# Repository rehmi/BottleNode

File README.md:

# BottleNode
#### An interactive network node for immersive experiences built around a Seeed Studio XIAO ESP32-S3

This repository contains the design and code for the BottleNode project. The project is structured into two main directories:

- `AllInOne_test`: This directory contains an Arduino program to test the BottleNode hardware. You will want to install the following Arduino libraries using the Library Manager (`Sketch` -> `Include Library` -> `Manage Libraries...`):
	* `Adafruit NeoPixel` (by Adafruit)
	* `LiteLED` (by Xylopyrographer)
	* `OSC` (by Adrian Freed)
	* `WS2812FX` (by Harm Aldick)

- The program also depends on the [ESP32-audioI2S library](https://github.com/schreibfaul1/ESP32-audioI2S), which you can install in the Arduino IDE by following these steps:

 	1. Download the latest release as a .zip from the repo `Releases` page [(link)](https://github.com/schreibfaul1/ESP32-audioI2S/archive/refs/tags/3.0.0.zip)
	2. Click on `Sketch` -> `Include Library` -> `Add .ZIP Library...` to add the library to your environment.
	
- `hw/BottleNode`: This directory contains the KiCAD project and associated files for the hardware design of the BottleNode. It includes 3D renderings of the board as PNG images and a PDF schematic of the board. You can view the schematic [here](hw/BottleNode/BottleNode%20schematic.pdf).

	Renderings of the top and bottom of the PCB:

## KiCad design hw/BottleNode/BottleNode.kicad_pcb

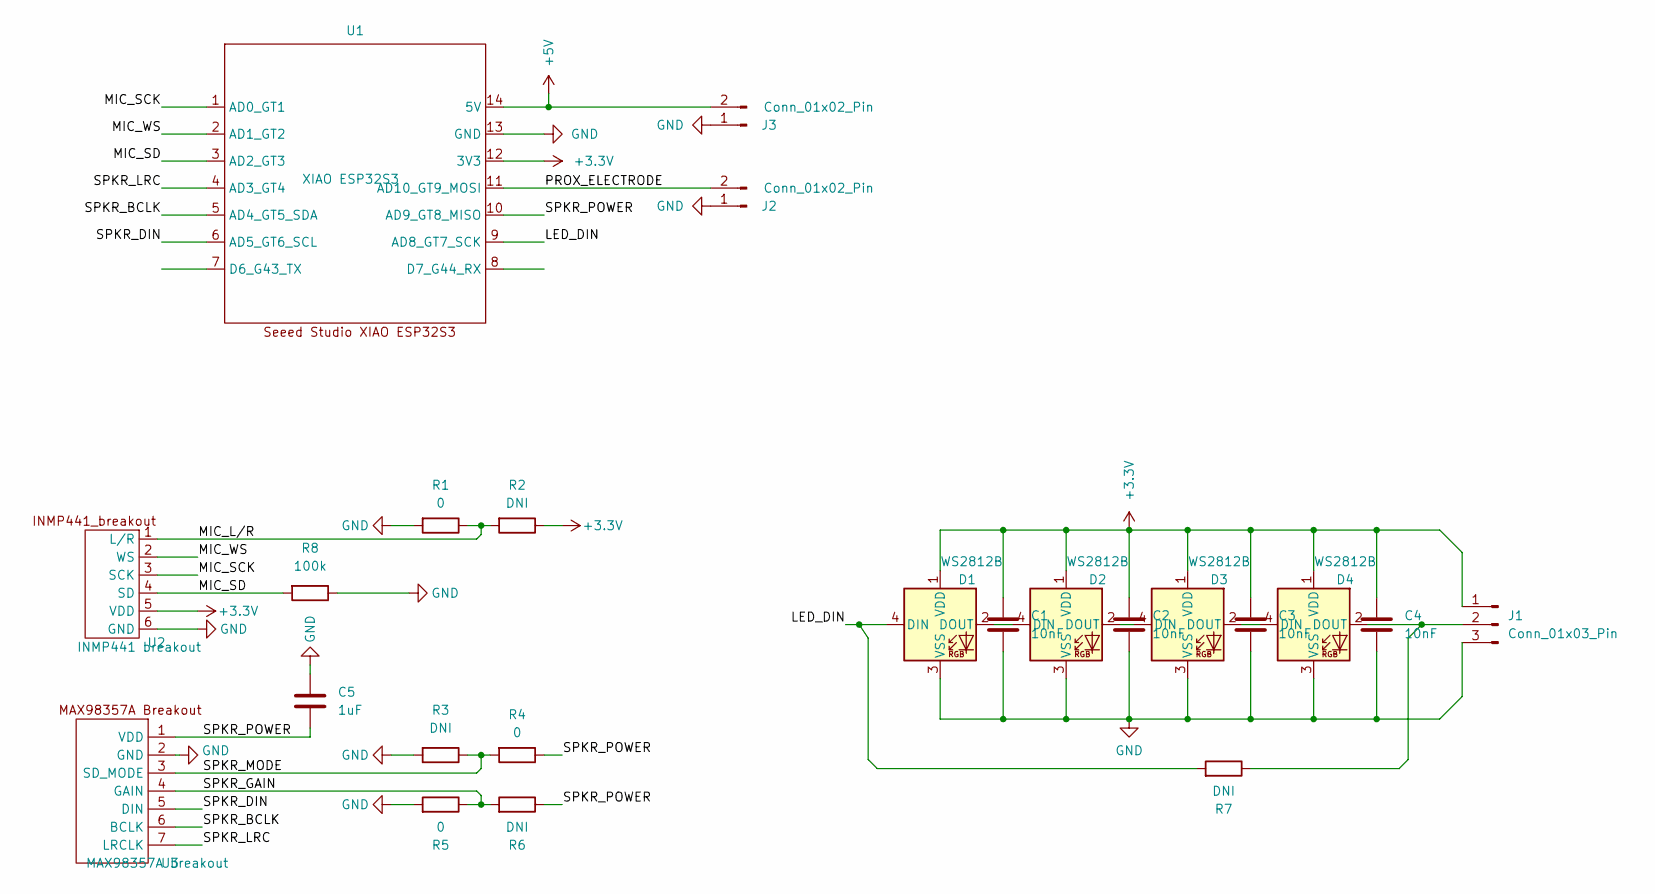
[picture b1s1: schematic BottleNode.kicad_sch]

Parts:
C1, C2, C3, C4: 10nF; C_0603_1608Metric_Pad1.08x0.95mm_HandSolder
C5: 1uF; C_0603_1608Metric_Pad1.08x0.95mm_HandSolder
D1, D2, D3, D4: WS2812B; LED_WS2812B_PLCC4_5.0x5.0mm_P3.2mm
J1: Conn_01x03_Pin; PinHeader_1x03_P2.54mm_Vertical
J2, J3: Conn_01x02_Pin; PinHeader_1x02_P2.54mm_Vertical
R1, R4, R5: 0; R_0603_1608Metric_Pad0.98x0.95mm_HandSolder
R2, R3, R6, R7: DNI; R_0603_1608Metric_Pad0.98x0.95mm_HandSolder
R8: 100k; R_0603_1608Metric_Pad0.98x0.95mm_HandSolder
U1: XIAO ESP32S3; XIAO-Generic-Thruhole-14P-2.54-21X17.8MM
U2: INMP441 breakout; INMP441_breakout
U3: MAX98357A breakout; MAX98357A_adafruit_breakout

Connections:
+3.3V: C1.1, C2.1, C3.1, C4.1, D1.1 (VDD), D2.1 (VDD), D3.1 (VDD), D4.1 (VDD), J1.1, R2.1, U1.12 (3V3), U2.5 (VDD)
+5V: J3.2, U1.14 (5V)
/LED_DIN: D1.4 (DIN), R7.2, U1.9 (AD8_GT7_SCK)
/MIC_L/R: R1.1, R2.2, U2.1 (L/R)
/MIC_SCK: U1.1 (AD0_GT1), U2.3 (SCK)
/MIC_SD: R8.2, U1.3 (AD2_GT3), U2.4 (SD)
/MIC_WS: U1.2 (AD1_GT2), U2.2 (WS)
/PROX_ELECTRODE: J2.2, U1.11 (AD10_GT9_MOSI)
/SPKR_BCLK: U1.5 (AD4_GT5_SDA), U3.6 (BCLK)
/SPKR_DIN: U1.6 (AD5_GT6_SCL), U3.5 (DIN)
/SPKR_GAIN: R5.1, R6.2, U3.4 (GAIN)
/SPKR_LRC: U1.4 (AD3_GT4), U3.7 (LRCLK)
/SPKR_MODE: R3.1, R4.2, U3.3 (SD_MODE)
/SPKR_POWER: C5.2, R4.1, R6.1, U1.10 (AD9_GT8_MISO), U3.1 (VDD)
GND: C1.2, C2.2, C3.2, C4.2, C5.1, D1.3 (VSS), D2.3 (VSS), D3.3 (VSS), D4.3 (VSS), J1.3, J2.1, J3.1, R1.2, R3.2, R5.2, R8.1, U1.13 (GND), U2.6 (GND), U3.2 (GND)
unnamed: D1.2 (DOUT), D2.4 (DIN)
unnamed: D2.2 (DOUT), D3.4 (DIN)
unnamed: D3.2 (DOUT), D4.4 (DIN)
unnamed: D4.2 (DOUT), J1.2, R7.1

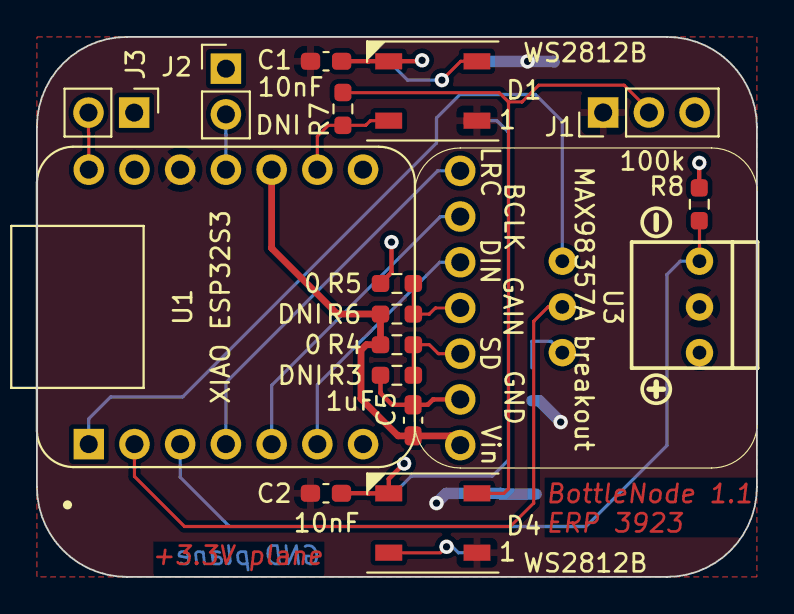
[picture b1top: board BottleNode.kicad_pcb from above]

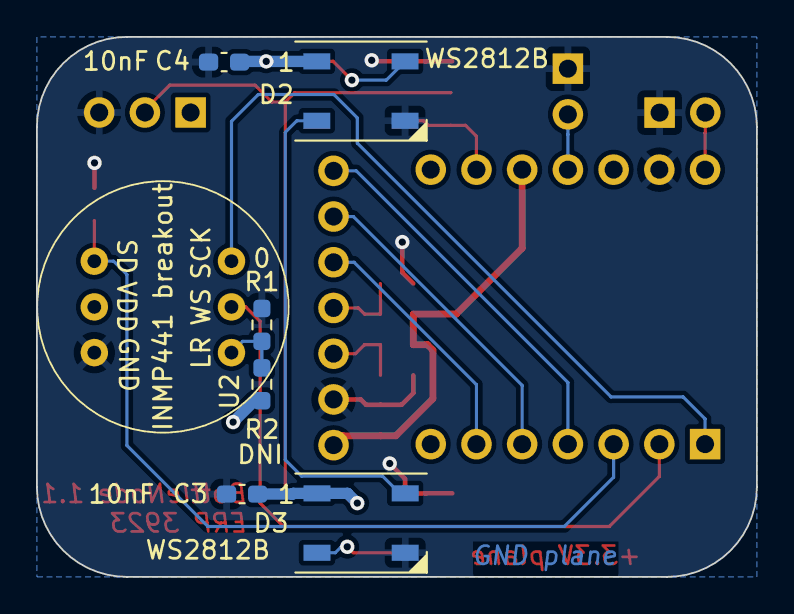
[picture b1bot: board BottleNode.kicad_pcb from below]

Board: 2 copper layers, 40.0 x 30.0 mm, 23 parts (7 on the bottom side), 19 nets.

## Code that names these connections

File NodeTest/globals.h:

#include <ArduinoOTA.h>
#include <ESPmDNS.h>
#include <WiFi.h>
#include <WiFiMulti.h>
#include <WiFiUdp.h>
#include "Arduino.h"

#include <Audio.h>

// Fix LED defns for the XIAO_ESP32S3
#undef BUILTIN_LED
#undef LED_BUILTIN
#define LED_BUILTIN 21
#define BUILTIN_LED 21

#define MIC_SCK		((gpio_num_t)1)
#define MIC_WS		((gpio_num_t)2)
#define MIC_SD		((gpio_num_t)3)
#define SPKR_LRC	((gpio_num_t)4)
#define SPKR_BCLK	((gpio_num_t)5)
#define SPKR_DIN	((gpio_num_t)6)
#define LED_DIN		((gpio_num_t)7)
#define SPKR_POWER	((gpio_num_t)8)
#define PROX_ELECTRODE	((gpio_num_t)9)

#define LED_COUNT 5
#define USE_LiteLED 1
#define USE_WS2812FX 0

extern float touchfactor;

#define MAX98357_RESET_HACK

#define BUFLEN 256

extern float output_attenuation;

extern void setup_OTA(void);
extern void setup_WiFi(void);
extern void setup_OSC(void);
extern void setup_I2S(void);
extern void setup_LEDS(void);
extern void setup_touch(void);
extern void setup_audio(void);
extern void setup_webdav(void);

extern void loop_OTA(void);
extern void loop_WiFi(void);
extern void loop_OSC(void);
extern void loop_I2S(void);
extern void loop_LEDS(void);
extern void loop_touch(void);
extern void loop_audio(void);
extern void loop_webdav(void);

extern void LED_ON(), LED_OFF(), LED_toggle();

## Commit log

2023-09-16 checking a whole bunch of sketches as a start
2023-09-19 preliminary schematic and PCB layout
2023-09-19 schematic and code fragments now agree on pinouts
2023-09-20 MAX98357_RESET_HACK to mitigate output shutdowns
2023-09-21 AllInOne_test = I2S passthru + LEDs + cap sensing
2023-09-21 swap SPKR_POWER/TOUCH_PIN in AllInOne_test/sch/pcb
2023-09-27 refactored AllInOne_test into several modules
2023-09-28 .gitignore additions for clarity
2023-09-28 update LED behavior in OSC.cpp stub
2023-09-28 update BottleNode-schematic.pdf to match .sch file
2023-09-28 add a trivial TouchOSC control panel for testing
2023-09-28 pin defs now in globals.h; added myAudioI2S.cpp
2023-09-29 rev 1.1 of schematic and PCB layout with BOM
2023-09-29 updated schematic PDF and 3D renderings
2023-09-29 final tweaks on PCB v1.1
2023-09-30 change occurrences of "myAudioI2S" to "audio"
2023-09-30 rev 1.1.1 - move config resistors away from header
2023-10-04 Functional LED/Wifi
    Function WIFI and LED on my local esp32.
2023-10-04 Running RGB and brightness
2023-10-04 Outputs using OSCLite now sent back to Max in OSCL.cpp
2023-10-04 Max patch added to the project
2023-10-05 Adding back in the audio and i2s
2023-10-05 Adding music playing commands and a webserver to host the music directory stream url.
2023-10-06 Adding in IP addrss getting from arduino and max
2023-10-07 updated instructions for library installation
2023-10-09 Adding batch send to send commands to all devices rather than just one
2023-10-09 Adding a pusher for current IP addresses as they respond to a request to identify
2023-10-10 Adding in some Max control stuff
2023-10-10 Commit for the night - trying to debug audio delays
2023-10-11 Adding in capability for touchfactor feedback. Also fixed bug with loop_i2s(). Also cleaned up Max layout. And separated the commands so they are ip specific.
2023-10-11 adding a branch and run directory for the live installation
2023-10-11 Removing IP address fixing and Adding sound tracks
2023-10-11 Fixing the IPv6 to IPv4
2023-10-11 Removing some console.log()
2023-10-12 Adding many nodes and control for music into max
2023-10-12 AllInOne_test for initial group testing
2023-10-12 Fixed webserver bugggg
2023-10-12 switch to 32kbps test stream
2023-10-12 add TODO list
2023-10-12 cleanup old files
2023-10-12 NodeTest now plays from SPIFFS (/default.aac)
2023-10-12 NodeTest audio loop of /default.aac on SPIFFS
2023-10-13 Pushing code for 10_12_2023 Live run
2023-10-13 Added WebDAV server to NodeTest.ino in webdav.cpp
2023-10-14 Adding the last of the changes (did not push this to all nodes).
    Adding the last of the changes (did not push this to all nodes).
